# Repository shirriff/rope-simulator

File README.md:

# Core Rope Simulator

This repository documents a core rope simulator for the Apollo Guidance Computer. This simulator was built by Raytheon around 1970 and plugged into the Apollo Guidance Computer in place of the 6 core rope modules. It allowed an external computer to provide the rope data.

The [Apollo Guidance Computer](https://en.wikipedia.org/wiki/Apollo_Guidance_Computer)  is the famous computer used to navigate to the Moon during the Apollo missions.
Its programs were stored in a 36K word ROM, constructed from [core rope memory](https://en.wikipedia.org/wiki/Core_rope_memory); data was stored by putting wires through or around magenetic cores to store 1's or 0's.

Each core rope needed to be constructed by hand  (with some mechanical help), a very slow process. Thus, for development and ground testing, a different mechanism was used: the core rope simulator.
The simulator allowed an external computer to simulate the core rope, allowing the AGC to run arbitrary programs.

The simulator consists of two boxes that plug into the AGC's core rope slots, providing an interface between the AGC's address and data lines and the external computer. Each box has a MIL Spec 20-39P receptacle for connection to the external computer (size 20, 39 pins). One box provides address information from the AGC, while the other box feeds 16 data bits into the AGC.

The [Portafam](http://www.klabs.org/history/ech/memos_misc/e-2402.pdf) is a different core rope simulator built by the MIT Instrumentation Laboratory in 1969. The Portafam has a totally different architecture internally.

## How core rope works

At a high level, core rope is simple: wires go through cores to indicate 1's, or bypass cores to indicate 0's, but the details get more complex.

The AGC uses 16 bit words (15 data bits and parity). The ropes hold 36K (36864) words.

The rope memory is organized as three ropes. Each rope consists of two separate modules, wired together by the AGC backplane into one unit electrically.
A module consists of 512 cores.
Each core has 12×16 data wires passing through (or around it), corresponding to 12 words stored per core. (Note the high density compared to regular (RAM) core memory, which holds 1 bit per core.)
Each group of 16 words is called a *strand*, so there are 12 strands per core.

To summarize, 6 modules × 512 cores per module × 12 strands per core = 36864 words.

## Properties of cores
Several properties of cores are important to this discussion.

 A core is magnetized into one of two states.
 Wires can be threaded through the core to change its state. When the opposite current is passed through a core, the core will flip to the opposite state. (If the current direction matches the core's state, the core does not flip but remains in the same state.)
 
When a core flips to the opposite state, this induces a current in a sense wire threaded through the core. If the core does not flip, no current is induced in the sense wire (except for noise current).

Cores have a hysteresis property. A low current will have no effect on a core. But a current above a threshold will flip the core to match the polarity of the current. 

The hysteresis property is important because it allows cores to be addressed using multiple wires. If there are multiple wires threaded through a core, the sum of the currents controls whether or not the core flips. An *inhibit* line with opposite current can cancel out the current from another line.

(Regular erasable core memory uses a "coincident-current" technique with an X/Y grid of select lines through the cores. An X line and a Y line are energized with half the necessary current. The core at the intersection of the X and Y lines has enough current to flip. Thus, a single core in the grid is selected through the X and Y lines.)

To access a word from the core rope, first the selected core is *set*, flipping it on.
The core rope uses seven address lines to select a particular core.
Each core has seven inhibit lines through it, corresponding to the address bits that should *not* be 1's.
Every core except the selected one will have at least one inhibit line 1, blocking the core from being set (flipped).

Somewhat unexpectedly, the value isn't read from core at this point, but during the reset phase, when the core is flipped back to its 0 state.
A reset signal is passed through all the cores. Only the core that was flipped during the set state will flip back during the reset state. This induces a current in all the sense wires (12 strands of 16 bits) that pass through that core. This allows the value of the core to be read out.

Finally, the 16 weak sense line signals are amplified by the sense amps and converted to the 16-bit digital output.

### Complications

There are several complications to this.

All 12 strands receive signals, but we want to read only one of the strands.
This is accomplished by the strand select signals: 12 signals that select the desired strand.
These signals block all the strands except the desired one (using a diode circuit, see [MIT's Role in Project Apollo, Vol. III](http://ibiblio.org/apollo/hrst/archive/1029.pdf) Fig 3-13), so only one strand passes its signal to the sense amp.

Similarly, six module select lines are used to select one of the six modules and short out the sense lines from the other five modules.

Note that 7 address lines select one of 128 cores. Each module consists of four planes of 128 cores, yielding 512 cores.
To select one of the four planes, four different reset lines are used, to reset just the core in the desired plane. Thus, only that plane is read.
Two set lines are used, one to set cores in planes A and B, and one for planes C and D. At set time, the reset
line blocks the undesired plane.
Thus, one core will be set.

Finally, in addition to the 7 address inhibit lines, there is an eighth address parity inhibit line.
The purpose of this is to ensure that every non-selected core gets two inhibit signals and is solidly inhibited. Otherwise, a core with just one inhibit line high might receive a bit of current, changing its magnetism slightly and introducing noise.

## Guide to documentation

Fixed memory is described in the AC Electronic LM Manual volume 2 starting at [4-594](https://archive.org/details/acelectroniclmma00acel_0/page/n275).

### Inhibit circuit

The inhibit circuit and return are described [here](https://archive.org/details/acelectroniclmma00acel_0/page/n279) and the schematic is [here](https://archive.org/details/acelectroniclmma00acel_0/page/n287).

### Strand and module select

The strand and module select circuits are described [here](https://archive.org/details/acelectroniclmma00acel_0/page/n296) and the schematics are [here](https://archive.org/details/acelectroniclmma00acel_0/page/n284) and [here](https://archive.org/details/acelectroniclmma00acel_0/page/n298).

### Sense amplifiers

The sense amplifiers are described [here](https://archive.org/details/acelectroniclmma00acel_0/page/n296) and the schematic is [here](https://archive.org/details/acelectroniclmma00acel_0/page/n298).

### Set and reset circuits

The set circuit and return are described [here](https://archive.org/details/acelectroniclmma00acel_0/page/n275) and [here](https://archive.org/details/acelectroniclmma00acel_0/page/n278) and the schematics are [here](https://archive.org/details/acelectroniclmma00acel_0/page/n282) and [here](https://archive.org/details/acelectroniclmma00acel_0/page/n291).

SET ENABLE is activated by ROP·T10·PHS4
and cleared by T01·PHS3 or TIMR (stop/alarm).
RESET ENABLE is activated by ROP·T05·PHS3
and cleared by T08 or GOJAM.
[schematic](https://archive.org/details/acelectroniclmma00acel_0/page/n277) 

The reset circuit and return are described [here](https://archive.org/details/acelectroniclmma00acel_0/page/n275) and [here](https://archive.org/details/acelectroniclmma00acel_0/page/n278) and the schematic is [here](https://archive.org/details/acelectroniclmma00acel_0/page/n289).

The documented description of the set and reset circuits is incomplete.
Since each set line passes through two planes, a mechanism is required to prevent the core in the wrong plane from being set.
This is accomplished by triggering the reset line in the other plane at the same time as the set line.
This is implemented by CLEARA/CLEARB/CLEARC/CLEARD (unrelated to the clear line), shown on schematic [4-208](https://archive.org/details/acelectroniclmma00acel_0/page/n281).
Thus, there are two different reset lines triggered at different times during a fixed memory access.

### Clear circuit

A *clear* line passes through all the cores; it can be used to reset all the cores.
The clear line is used only for an "aborted" fixed memory access. For a quarter code instruction, a fixed memory cycle can start before it is determined that erasable memory is being accessed. In this case, the clear line resets the fixed core that was set. ([Summary](https://archive.org/details/acelectroniclmma00acel_0/page/n275) and [details](https://www.ibiblio.org/apollo/Documents/dd_memo_376.pdf).) The schematic is [here](https://archive.org/details/acelectroniclmma00acel_0/page/n293).

For example, the instruction `INCR K` has opcode `26000+K`. Since bit S12 is set, it looks like a fixed memory operation and the fixed memory cycle will start. However, it is a [quartercode](https://www.ibiblio.org/apollo/assembly_language_manual.html#Instruction_Representation) instruction on erasable memory.
When the instruction is decoded, the clear line is used to clean up the partial fixed memory access.

CLROPE is generated by ROP'·T02 (if a fixed read cycle started with ROP·T10) and cleared by T03 (along with some other conditions), see [figure 4-206](https://archive.org/details/acelectroniclmma00acel_0/page/n277)

## Summary

Putting this all together, the module select lines select one of 6 modules. The reset lines select one of four planes in the module. The 7 address lines select one of 128 cores in the plane. The strand select lines select one of 12 strands of 16 bit wires through the core. This yields 6 × 4 × 128 × 12 = 36864 words in total.

## Addressing

Instructions have a 12-bit address field, allowing 4K words to be directly addressed. The full address space is accessed through a complex bank system. The bank system is not particularly relevant to the simulator; instead, the internal addressing is what's important.

In the following description, the memory bank registers have been decoded ([discussion](https://archive.org/details/acelectroniclmma00acel_0/page/n95), [logic](https://archive.org/details/acelectroniclmma00acel_0/page/n101)) to generate a 16-bit fixed (i.e. rope) address.
The 36K of rope storage is mapped into this address space linearly, without holes, starting at address 0.

The address consists of signals S1 (low bit) through S10 and F11 through F16 (high bit). Bits S1 through S10 are the low nine bits from the "normal" address (in the S register) and bits F11-F16 are fixed address bits generated from the fixed register.
See discussion starting at [page 4-571](https://archive.org/details/acelectroniclmma00acel_0/page/n252) of *AC Electronic LM Manual Volume 2*.

The low order bits S1 through S7 of the address select one of the 128 cores in a rope module. Bits S8 and S9 select one of the four planes in a module. Thus, the bottom 9 bits select one of 512 words in a straighforward way.

The tricky part of addressing is the 12 strands and 6 modules don't map cleanly onto binary bits. Considerable logic is required in the AGC to convert a binary address into strands and modules without holes in the address space, and the rope simulator reverses this logic.

S10 and F11 through F16 are used to generate the 12 strand signals (slightly encoded), 2 module group select signals, and three rope select signals. The 6 bits generate 72 output patterns in sequence, each selecting a 512-word block of memory.

The strand addressing sequence starts with strand 1, low module, rope R. It proceeds through the 12 strands in sequence in the low module, and then the high module, for address bits 000000 through 0010111. The next 24 address blocks go through the same sequence in rope S. Finally, the sequence is repeated in rope T.

The AGC's rope, module, and strand selector gates are shown on [figure 4-209](https://archive.org/details/acelectroniclmma00acel_0/page/n284) of *AC Electronic LM Manual Volume 2*. This circuit uses over 50 NOR gates on module A15.

The simulator reverses this entire process. It detects the inhibit, set, reset, module select, and rope select signals, and generates a linear 16-bit address from them.

## Timing

A memory cycle consists of twelve cycles of 0.977 microseconds, 11.7 microseconds in total.
The fixed memory timing diagram is [figure 4-197](https://archive.org/details/acelectroniclmma00acel_0/page/n257), schematic [figure 4-206](https://archive.org/details/acelectroniclmma00acel_0/page/n277) and discussion at [page 4-595](https://archive.org/details/acelectroniclmma00acel_0/page/n276).

Inhibit lines are enabled starting at time T08 until T01.
The set line is enabled from T10 to T01.Strand lines are enabled from T02 to T08 via STRGAT.The reset line is triggered from T05 to T08.

The sense amp reads the data from T06 to T07.

The signals happen at particular phases during the T cycles, using PHS3.

IHENV set by T08
STRGAT set by ROP and T02, cleared by T08.

## The simulator

The rope simulator consists of two boxes.
Each box takes up three module slots.
One box sends address signals from the AGC to the external computer, while the other box sends a data word from the external computer to the AGC.
The first box (which I'll call the address box) is mounted in AGC slots B1/B3/B5.
The second box (which I'll call the data box) is mounted in AGC slots B2/B4/B6.
The address box is considerably more complex than the data box.

Each box has a round connector (MIL Spec 20-39P with unusual keying) for communication with the external computer.
The address box sends signals to the external computer using a a7820 differential line driver, while the data box receives signals from the external computer using a 7830 differential line receiver.
Power is supplied to both boxes through the address box connector.

The AGC's core rope circuitry produces several complications for the simulator. 
First, the AGC doesn't provide a convenient memory bus;
there aren't address and data lines with power and ground.
Instead, the signals on the rope connectors are current pulses designed to drive the cores directly.
Second, each pair of rope modules is electrically wired together (by the AGC backplane) to form one rope unit, and each signal forms a loop through both modules.
Thus, both simulator boxes must work together to complete the circuit for each signal.
Finally, the AGC provides a separate signal return path for each rope. Thus, the simulator can't simply feed signals to ground, but must use a diode matrix on each signal to handle the multiple return paths.

## Construction

The simulator consists of two metal boxes that slide into the AGC.
Each box has a round 39-pin connector for communication with the external computer.

The simulator is constructed with techniques that may seem unusual today.
The construction is a combination of wirewrapped TTL chips and cordwood analog circuitry (mostly pulse transformers).

The logic circuitry is built from 5400-series TTL chips.

### Dipstik

The chips are mounted using a product called *Dipstik*, which was briefly popular in the early 1970s.
Each Dipstik unit holds five DIP chips. The Dipstik has wirewrap pins underneath for the circuit wiring.
In addition, the Dipstik has solder lugs on top, which are used to connect resistors and capacitors.

The Dipstik consists of two parts: a top and bottom. Each part has two rows of gold contacts.
Five ICs are placed on the top, and held in place by a retaining bar. The inside of each IC pin is held against a gold contact on the top piece.
The top is placed upside down on the bottom part and screwed into place.
Gold contacts on the bottom press against the outside of each IC pin.
Thus, each IC pin is sandwiched between two gold contacts.

The Dipstik provides a structured way of organizing the ICs.
Each Dipstik holds 5 ICs, labeled A through E.
There are 18 pin positions for each IC, so 14-pin ICs have two unused pairs between ICs, while 16-pin ICs have one unused pair.
The pins are labeled on both sides of the Dipstik for convenience; a number like 8-10 indicates pin 8 for a 16-pin IC and pin 10 for a 14-pin IC.

Each Dipstik is labeled sequentially: DS1, DS2, etc.
Thus, a particular IC pin can be specified by the Dipstik number, IC letter, and pin number, such as DS1-E-3 for pin 3 of IC E in Dipstik 1.

Unfortunately Dipstiks have several problem (which probably led to the short life of the product).
First, the tabs holding the retaining bar on the top part break. The retaining bar remains stuck at the bottom of the Dipstik and half of the ICs stay upside down in the Dipstik when the top is remove.
This isn't a huge problem, as long as the metal fragments are removed so they don't cause shorts.
Second, the ICs don't make good contact with the top. (This can be seen by testing connectivity of the power or ground pins on the top.) The solution is to bend the pins of each IC inward slightly so they grip the top more firmly.
Third, we received reports that the screw-down mechanism doesn't provide as much pressure in the middle, causing worse connections in the middle ICs.

### Connector

Each of the six AGC module slots has a connector for the rope module.
The connector has four rows of 24 female Malco mini-wasp contacts.
To match this, each rope simulator box has three sets of 4x24 male Malco pins.

## Simulator timing
The set line is enabled from T10 to T01. This triggers a signal to the external computer from T11 to T07.
 A one-shot is triggered 550 ns after STRGAT, and when STRGAT drops, the flip flop reset signal is generated.
 The clear signal is enabled at ???; it is gated by a one-shot triggered off STRGAT for T03.

## References

* [AC Electronic LM Manual Volume 2](https://archive.org/details/acelectroniclmma00acel_0/page/n245) has lots of information on the AGC's fixed memory, including schematics.

* [MIT's Role in Project Apollo, Vol. III: Computer Subsystem](https://www.ibiblio.org/apollo/hrst/archive/1029.pdf). Fixed memory is discussed in Section 3.5.2. Core rope simulators are discussed briefly in Section 5.3.1.

[Core rope wiring diagram](https://archive.org/stream/agc_handbook_jp2#page/n112/mode/2up)

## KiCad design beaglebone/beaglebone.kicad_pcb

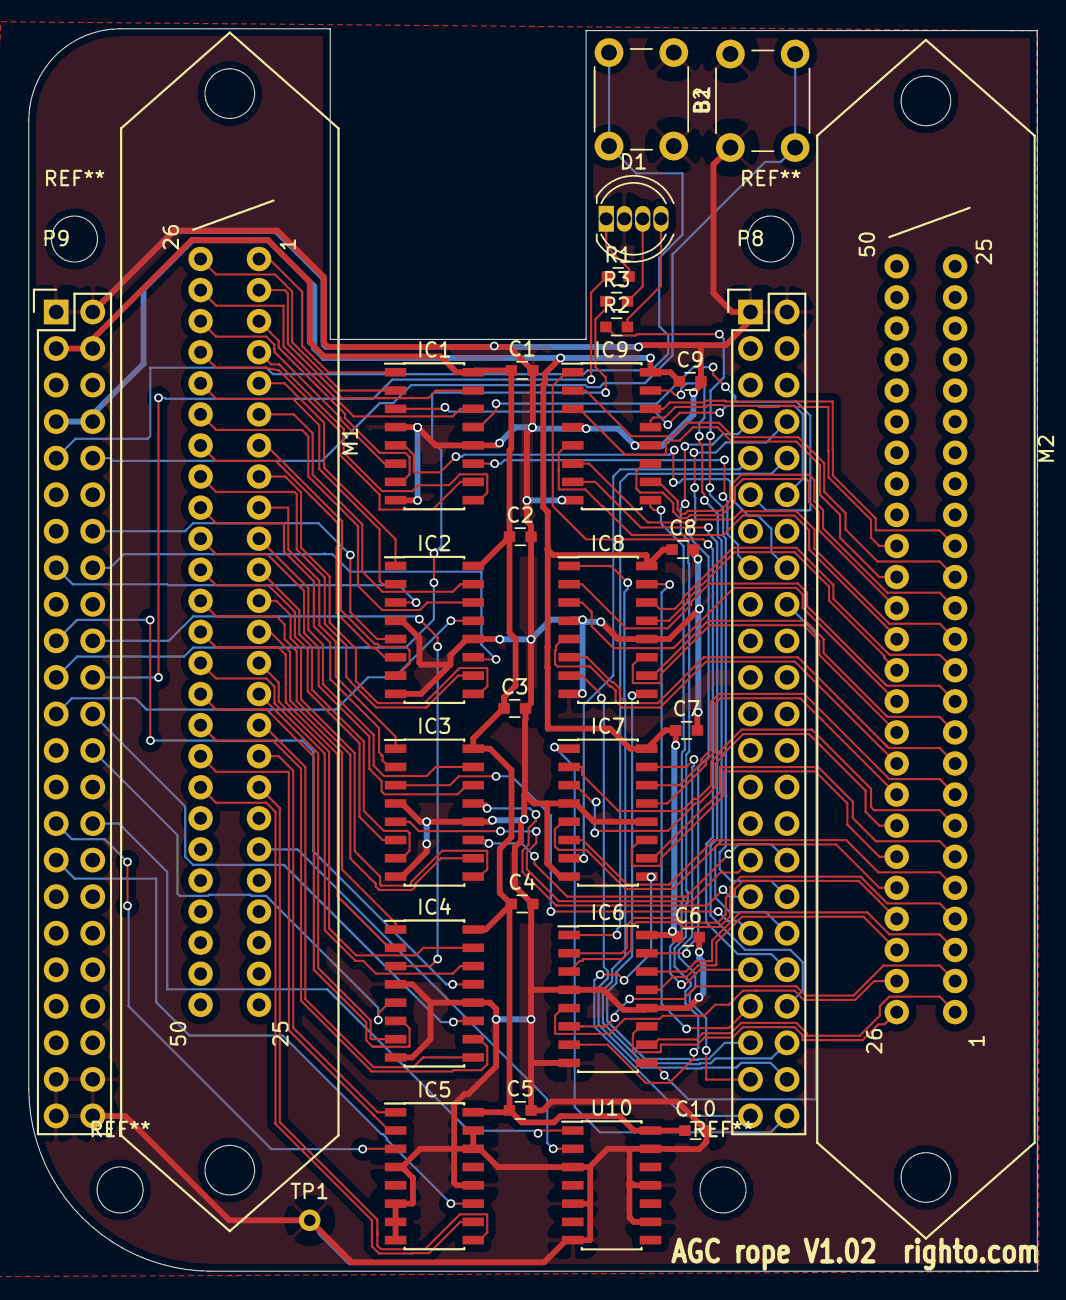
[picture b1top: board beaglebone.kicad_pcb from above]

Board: 2 copper layers, 70.1 x 86.4 mm, 31 parts (0 on the bottom side), 115 nets.

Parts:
B1, B2: SW_Push; SW_PUSH_6mm
C1, C2, C3, C4, C5, C6, C7, C8, C9, C10: .1UF; C_0603
D1: LED_RCGB; LED_D5.0mm-4
IC1, IC2, IC3, IC4, IC5: AM26C32; SOIC-16_3.9x9.9mm_Pitch1.27mm
IC6, IC7, IC8, IC9: AM26C31; SOIC-16_3.9x9.9mm_Pitch1.27mm
M1: 50-PIN-CENTRONICS-FFEMALE; CENTRONICS-50-F
M2: 50-PIN-CENTRONICS-MMALE; CENTRONICS-50-M
P8, P9: BeagleBone_Black_Header; Socket_BeagleBone_Black
R1, R2, R3: 220; C_0603
TP1: TestPoint; Measurement_Point_Round-TH_Small
U10: 74LVC07; SOIC-14_3.9x8.7mm_Pitch1.27mm

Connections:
+3V3: C1.1, C2.1, C3.1, C4.1, C5.1, C10.1, IC1.16, IC2.16, IC3.16, IC4.16, IC5.16, P9.3, P9.4, U10.14
/IL1: IC1.3, P8.12
/IL1+: IC1.2, M1.26
/IL1-: IC1.1, M1.1
/IL2: IC1.13, P8.11
/IL2+: IC1.14, M1.27
/IL2-: IC1.15, M1.2
/IL3: IC1.5, P8.16
/IL3+: IC1.6, M1.28
/IL3-: IC1.7, M1.3
/IL4: IC1.11, P8.15
/IL4+: IC1.10, M1.29
/IL4-: IC1.9, M1.4
/IL5: IC2.3, P9.15
/IL5+: IC2.2, M1.30
/IL5-: IC2.1, M1.5
/IL6: IC2.13, P9.23
/IL6+: IC2.14, M1.31
/IL6-: IC2.15, M1.6
/IL7: IC2.5, P9.14
/IL7+: IC2.6, M1.32
/IL7-: IC2.7, M1.7
/addr_okay: IC5.11, P9.31
/addr_okay+: IC5.10, M1.43
/addr_okay-: IC5.9, M1.18
/b: P8.34, R2.1
/clear: IC5.3, P9.29
/clear+: IC5.2, M1.42
/clear-: IC5.1, M1.17
/g: P9.21, R3.1
/plane0: IC2.11, P9.16
/plane0+: IC2.10, M1.33
/plane0-: IC2.9, M1.8
/plane1: IC3.3, P8.35
/plane1+: IC3.2, M1.34
/plane1-: IC3.1, M1.9
/plane2: IC3.13, P8.33
/plane2+: IC3.14, M1.35
/plane2-: IC3.15, M1.10
/plane3: IC3.5, P8.31
/plane3+: IC3.6, M1.36
/plane3-: IC3.7, M1.11
/plane4: IC3.11, P8.32
/plane4+: IC3.10, M1.37
/plane4-: IC3.9, M1.12
/plane5: IC4.3, P9.20
/plane5+: IC4.2, M1.38
/plane5-: IC4.1, M1.13
/plane6: IC4.13, P9.19
/plane6+: IC4.14, M1.39
/plane6-: IC4.15, M1.14
/plane7: IC4.5, P9.26
/plane7+: IC4.6, M1.40
/plane7-: IC4.7, M1.15
/plane8: IC4.11, P9.24
/plane8+: IC4.10, M1.41
/plane8-: IC4.9, M1.16
/r: P9.22, R1.1
/red: P9.30, U10.1
/red_out: M1.20, U10.2
/sense1: IC6.9, P8.18
/sense1+: IC6.10, M2.1
/sense1-: IC6.11, M2.26
/sense2: IC6.7, P8.7
/sense2+: IC6.6, M2.2
/sense2-: IC6.5, M2.27
/sense3: IC6.15, P8.8
/sense3+: IC6.14, M2.3
/sense3-: IC6.13, M2.28
/sense4: IC6.1, P8.10
/sense4+: IC6.2, M2.4
/sense4-: IC6.3, M2.29
/sense5: IC7.7, P8.9
/sense5+: IC7.6, M2.5
/sense5-: IC7.5, M2.30
/sense6: IC7.9, P8.45
/sense6+: IC7.10, M2.6
/sense6-: IC7.11, M2.31
/sense7: IC7.1, P8.46
/sense7+: IC7.2, M2.7
/sense7-: IC7.3, M2.32
/sense8: IC7.15, P8.43
/sense8+: IC7.14, M2.8
/sense8-: IC7.13, M2.33
/sense9: IC8.7, P8.44
/sense9+: IC8.6, M2.9
/sense9-: IC8.5, M2.34
/sense10: IC8.9, P8.41
/sense10+: IC8.10, M2.10
/sense10-: IC8.11, M2.35
/sense11: IC8.1, P8.42
/sense11+: IC8.2, M2.11
/sense11-: IC8.3, M2.36
/sense12: IC8.15, P8.39
/sense12+: IC8.14, M2.12
/sense12-: IC8.13, M2.37
/sense13: IC9.7, P8.40
/sense13+: IC9.6, M2.13
/sense13-: IC9.5, M2.38
/sense14: IC9.9, P8.37
/sense14+: IC9.10, M2.14
/sense14-: IC9.11, M2.39
/sense15: IC9.1, P8.38
/sense15+: IC9.2, M2.15
/sense15-: IC9.3, M2.40
/sense16: IC9.15, P8.36
/sense16+: IC9.14, M2.16
/sense16-: IC9.13, M2.41
GNDD: B1.1, B2.1, C1.2, C2.2, C3.2, C4.2, C5.2, C6.2, C7.2, C8.2, C9.2, C10.2, D1.2, IC1.4, IC1.8, IC1.12, IC2.4, IC2.8, IC2.12, IC3.4, IC3.8, IC3.12, IC4.4, IC4.8, IC4.12, IC5.4, IC5.6, IC5.7, IC5.8, IC5.12, IC5.14, IC5.15, IC6.4, IC6.8, IC6.12, IC7.4, IC7.8, IC7.12, IC8.4, IC8.8, IC8.12, IC9.4, IC9.8, IC9.12, P8.1, P8.2, P9.1, P9.2, P9.43, P9.44, P9.45, P9.46, TP1.1, U10.3, U10.5, U10.7, U10.9, U10.11, U10.13
unnamed: D1.1, R1.2
unnamed: D1.3, R3.2
unnamed: D1.4, R2.2
PWR_BUT: B1.2, P9.9
SYS_5V: C6.1, C7.1, C8.1, C9.1, IC6.16, IC7.16, IC8.16, IC9.16, P9.7, P9.8
SYS_RESETN: B2.2, P9.10

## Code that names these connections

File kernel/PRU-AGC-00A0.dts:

// DTS overlay for the AGC rope interface.
//
// Compile with:
// dtc -O dtb -I dts -o /lib/firmware/PRU-AGC-00A0.dtbo -b 0 -@ PRU-AGC-00A0.dts

/dts-v1/;
/plugin/;

/{
       compatible = "ti,beaglebone", "ti,beaglebone-black";
       part-number = "DM-GPIO-Test";
       version = "00A0";

  exclusive-use =
         "P8_18", // sense1
         "P8_7", // sense2
         "P8_8", // sense3
         "P8_10", // sense4
         "P8_9", // sense5
         "P8_45", // sense6
         "P8_46", // sense7
         "P8_43", // sense8
         "P8_44", // sense9
         "P8_41", // sense10
         "P8_42", // sense11
         "P8_39", // sense12
         "P8_40", // sense13
         "P8_37", // sense14
         "P8_38", // sense15
         "P8_36", // sense16
         "P8_12", // il1
         "P8_11", // il2
         "P8_16", // il3
         "P8_15", // il4
         "P9_15", // il5
         "P9_23", // il6
         "P9_14", // il7
         "P9_16", // plane0
         "P8_35", // plane1
         "P8_33", // plane2
         "P8_31", // plane3
         "P8_32", // plane4
         "P9_20", // plane5
         "P9_19", // plane6
         "P9_26", // plane7
         "P9_24", // plane8
         "P9_31", // addr_okay
         "P9_29", // clear
         "P9_30", // red
         "P9_22", // r
         "P9_21", // g
         "P8_34", // b
         "P9_25", // test
        "pru0";

       fragment@0 {
             target = <&am33xx_pinmux>;
            
             __overlay__ {
                  pinctrl_test: DM_GPIO_Test_Pins {
			pinctrl-single,pins = <
         0x08C 0x0f /* P8_18 sense1 - gpio2[1] - output */
         0x090 0x0f /* P8_7 sense2 - gpio2[2] - output */
         0x094 0x0f /* P8_8 sense3 - gpio2[3] - output */
         0x098 0x0f /* P8_10 sense4 - gpio2[4] - output */
         0x09C 0x0f /* P8_9 sense5 - gpio2[5] - output */
         0x0A0 0x0f /* P8_45 sense6 - gpio2[6] - output */
         0x0A4 0x0f /* P8_46 sense7 - gpio2[7] - output */
         0x0A8 0x0f /* P8_43 sense8 - gpio2[8] - output */
         0x0AC 0x0f /* P8_44 sense9 - gpio2[9] - output */
         0x0B0 0x0f /* P8_41 sense10 - gpio2[10] - output */
         0x0B4 0x0f /* P8_42 sense11 - gpio2[11] - output */
         0x0B8 0x0f /* P8_39 sense12 - gpio2[12] - output */
         0x0BC 0x0f /* P8_40 sense13 - gpio2[13] - output */
         0x0C0 0x0f /* P8_37 sense14 - gpio2[14] - output */
         0x0C4 0x0f /* P8_38 sense15 - gpio2[15] - output */
         0x0C8 0x0f /* P8_36 sense16 - gpio2[16] - output */
         0x030 0x27 /* P8_12 il1 - gpio1[12] - input */
         0x034 0x27 /* P8_11 il2 - gpio1[13] - input */
         0x038 0x27 /* P8_16 il3 - gpio1[14] - input */
         0x03C 0x27 /* P8_15 il4 - gpio1[15] - input */
         0x040 0x27 /* P9_15 il5 - gpio1[16] - input */
         0x044 0x27 /* P9_23 il6 - gpio1[17] - input */
         0x048 0x27 /* P9_14 il7 - gpio1[18] - input */
         0x04C 0x27 /* P9_16 plane0 - gpio1[19] - input */
         0x0D0 0x27 /* P8_35 plane1 - gpio0[8] - input */
         0x0D4 0x27 /* P8_33 plane2 - gpio0[9] - input */
         0x0D8 0x27 /* P8_31 plane3 - gpio0[10] - input */
         0x0DC 0x27 /* P8_32 plane4 - gpio0[11] - input */
         0x178 0x27 /* P9_20 plane5 - gpio0[12] - input */
         0x17C 0x27 /* P9_19 plane6 - gpio0[13] - input */
         0x180 0x27 /* P9_26 plane7 - gpio0[14] - input */
         0x184 0x27 /* P9_24 plane8 - gpio0[15] - input */
         0x190 0x26 /* P9_31 addr_okay - pr1_pru0_pru_r31_0 - input */
         0x194 0x26 /* P9_29 clear - pr1_pru0_pru_r31_1 - input */
         0x198 0x0f /* P9_30 red - gpio3[16] - output */
         0x150 0x0b /* P9_22 r - ehrpwm0A - output */
         0x154 0x0b /* P9_21 g - ehrpwm0B - output */
         0x0CC 0x0a /* P8_34 b - ehrpwm1B - output */
         0x1AC 0x05 /* P9_25 trigger - pr1_pru0_pru_r30_7 - output, mode 5 */
			>;
		  };
             };
       };

       fragment@1 {
		target = <&ocp>;
		__overlay__ {
	         	P8_18_pinmux {status = "disabled"; }; // sense1
	         	P8_7_pinmux {status = "disabled"; }; // sense2
	         	P8_8_pinmux {status = "disabled"; }; // sense3
	         	P8_10_pinmux {status = "disabled"; }; // sense4
	         	P8_9_pinmux {status = "disabled"; }; // sense5
	         	P8_45_pinmux {status = "disabled"; }; // sense6
	         	P8_46_pinmux {status = "disabled"; }; // sense7
	         	P8_43_pinmux {status = "disabled"; }; // sense8
	         	P8_44_pinmux {status = "disabled"; }; // sense9
	         	P8_41_pinmux {status = "disabled"; }; // sense10
	         	P8_42_pinmux {status = "disabled"; }; // sense11
	         	P8_39_pinmux {status = "disabled"; }; // sense12
	         	P8_40_pinmux {status = "disabled"; }; // sense13
	         	P8_37_pinmux {status = "disabled"; }; // sense14
	         	P8_38_pinmux {status = "disabled"; }; // sense15
	         	P8_36_pinmux {status = "disabled"; }; // sense16
	         	P8_12_pinmux {status = "disabled"; }; // il1
	         	P8_11_pinmux {status = "disabled"; }; // il2
	         	P8_16_pinmux {status = "disabled"; }; // il3
	         	P8_15_pinmux {status = "disabled"; }; // il4
	         	P9_15_pinmux {status = "disabled"; }; // il5
	         	P9_23_pinmux {status = "disabled"; }; // il6
	         	P9_14_pinmux {status = "disabled"; }; // il7
	         	P9_16_pinmux {status = "disabled"; }; // plane0
	         	P8_35_pinmux {status = "disabled"; }; // plane1
	         	P8_33_pinmux {status = "disabled"; }; // plane2
	         	P8_31_pinmux {status = "disabled"; }; // plane3
	         	P8_32_pinmux {status = "disabled"; }; // plane4
	         	P9_20_pinmux {status = "disabled"; }; // plane5
	         	P9_19_pinmux {status = "disabled"; }; // plane6
	         	P9_26_pinmux {status = "disabled"; }; // plane7
	         	P9_24_pinmux {status = "disabled"; }; // plane8
	         	P9_31_pinmux {status = "disabled"; }; // addr_okay
	         	P9_29_pinmux {status = "disabled"; }; // clear
	         	P9_30_pinmux {status = "disabled"; }; // red
	         	P9_22_pinmux {status = "disabled"; }; // r
	         	P9_21_pinmux {status = "disabled"; }; // g
	         	P8_34_pinmux {status = "disabled"; }; // b
	         	P9_25_pinmux {status = "disabled"; }; // test

			test_helper: helper {
				compatible = "bone-pinmux-helper";
				pinctrl-names = "default";
				pinctrl-0 = <&pinctrl_test>;
				status = "okay";
			};
		};
	};

	fragment@2 {
		target = <&epwmss0>;
		__overlay__ {
			status = "okay";
		};
	};

	fragment@3 {
		target = <&ehrpwm0>;
		__overlay__ {
			status = "okay";
		};
	};

	fragment@4 {
		target = <&epwmss1>;
		__overlay__ {
			status = "okay";
		};
	};

	fragment@5 {
		target = <&ehrpwm1>;
		__overlay__ {
			status = "okay";
		};
	};

	fragment@6 {
		target-path = "/";
		__overlay__ {
			reserved-memory {
				#address-cells = <1>;
				#size-cells = <1>;
				ranges;
				
				pru_comm_reserved: pru_comm_reserved@9fc00000 {
					reg = <0x9fc00000 0x20000>;
					no-map;
				};
			};
		};
	};
};

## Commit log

2019-05-28 Initial commit of AGC files
2019-05-28 Fix shared memory address: 0x9fc00000
2019-05-28 Address reading code.
2019-06-01 Create log_host/log_pru
2019-06-01 More test code.
2019-06-06 Update states, add state logging.
2019-06-06 Add more programs. main_host/main_pru are the "production" AGC programs.
2019-06-06 Add more states, change behavior of bufend.
2019-06-07 Add test programs, octal support.
2019-06-07 Switch main driver from testing to actual data. It mostly works now.
2019-06-09 Improve file loading, add FAULT log display.
2019-06-09 Change agc_setup to main_pru
2019-06-09 Add fault logging
2019-06-09 Address decoding utility
2019-06-09 Log processing utility to coalesce address accesses to see holes.
2019-06-09 Bunch of hacking on main routine, working version but not too clean.
2019-06-19 Add p9_25 as test pin.
2019-07-11 Check in files.
2019-07-11 Add schematics for rope simulator boxes and for beaglebone interface.
2019-07-11 Diagram.
2019-07-13 Move files to beaglebone subdirectory.
